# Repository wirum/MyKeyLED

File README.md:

# MyKeyLED
Your Pixels, Our Keychain  A simple OLED keychain that you can customize easily to your liking with GIFs, images, or short videos.

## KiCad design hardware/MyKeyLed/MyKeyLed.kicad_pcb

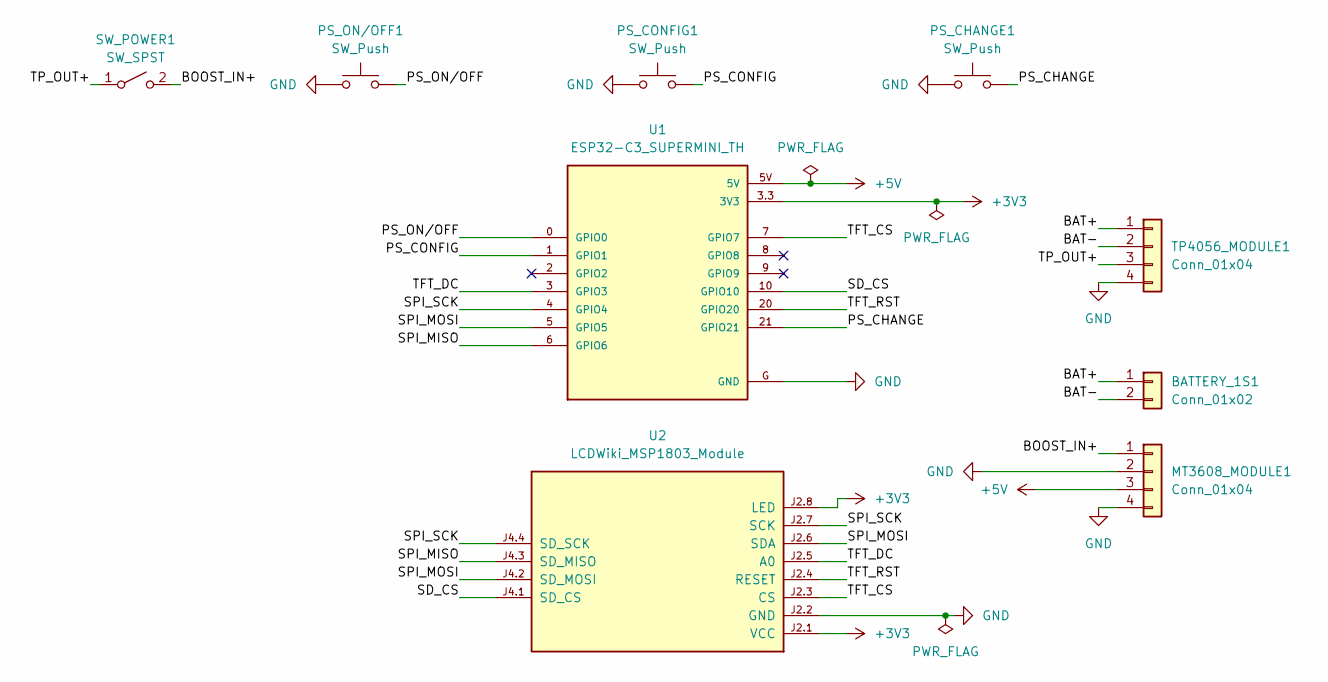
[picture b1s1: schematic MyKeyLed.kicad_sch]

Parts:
BATTERY_1S1: Conn_01x02; Battery_2Wire_2.54mm
MT3608_MODULE1: Conn_01x04; MT3608_Module_37x17mm
PS_CHANGE1: SW_Push; SW_PUSH-12mm
PS_CONFIG1: SW_Push; SW_PUSH-12mm
PS_ON/OFF1: SW_Push; SW_PUSH-12mm
SW_POWER1: SW_SPST; Switch_2Wire_2.54mm
TP4056_MODULE1: Conn_01x04; TP4056_USB-C_Protected_26x17mm
U1: ESP32-C3_SUPERMINI_TH; MODULE_ESP32-C3_SUPERMINI_TH
U2: LCDWiki_MSP1803_Module; LCDWiki_MSP1803_34.5x58mm

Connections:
+3V3: U1.3.3 (3V3), U2.J2.1 (VCC), U2.J2.8 (LED)
+5V: MT3608_MODULE1.3, U1.5V
/BAT+: BATTERY_1S1.1, TP4056_MODULE1.1
/BAT-: BATTERY_1S1.2, TP4056_MODULE1.2
/BOOST_IN+: MT3608_MODULE1.1, SW_POWER1.2 (B)
/PS_CHANGE: PS_CHANGE1.2, U1.21 (GPIO21)
/PS_CONFIG: PS_CONFIG1.2, U1.1 (GPIO1)
/PS_ON/OFF: PS_ON/OFF1.2, U1.0 (GPIO0)
/SD_CS: U1.10 (GPIO10), U2.J4.1 (SD_CS)
/SPI_MISO: U1.6 (GPIO6), U2.J4.3 (SD_MISO)
/SPI_MOSI: U1.5 (GPIO5), U2.J2.6 (SDA), U2.J4.2 (SD_MOSI)
/SPI_SCK: U1.4 (GPIO4), U2.J2.7 (SCK), U2.J4.4 (SD_SCK)
/TFT_CS: U1.7 (GPIO7), U2.J2.3 (CS)
/TFT_DC: U1.3 (GPIO3), U2.J2.5 (A0)
/TFT_RST: U1.20 (GPIO20), U2.J2.4 (RESET)
/TP_OUT+: SW_POWER1.1 (A), TP4056_MODULE1.3
GND: MT3608_MODULE1.2, MT3608_MODULE1.4, PS_CHANGE1.1, PS_CONFIG1.1, PS_ON/OFF1.1, TP4056_MODULE1.4, U1.G (GND), U2.J2.2 (GND)

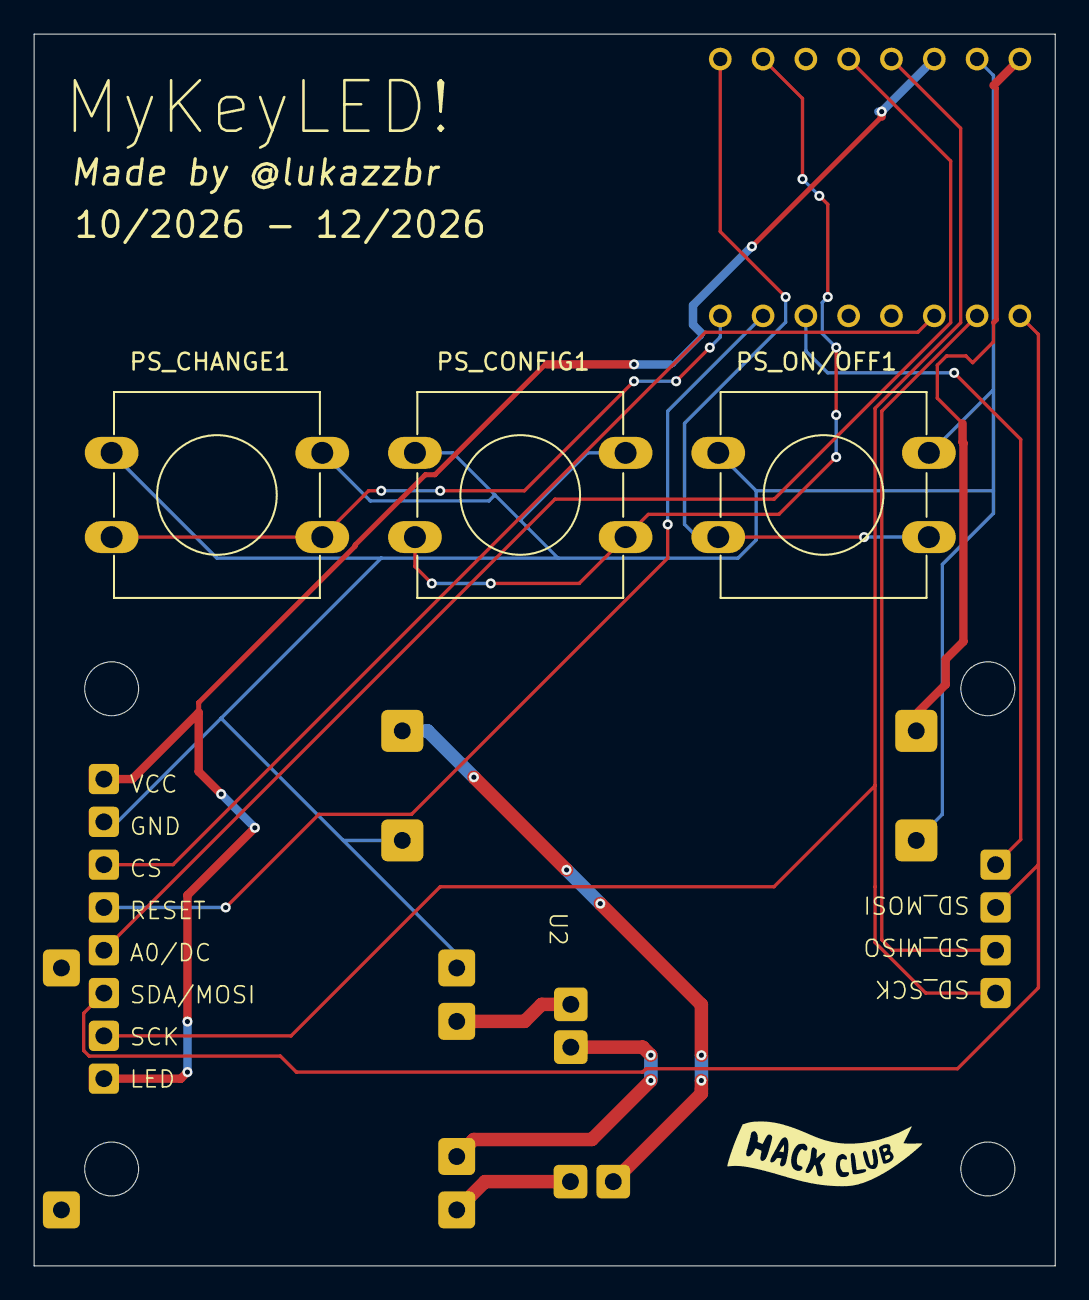
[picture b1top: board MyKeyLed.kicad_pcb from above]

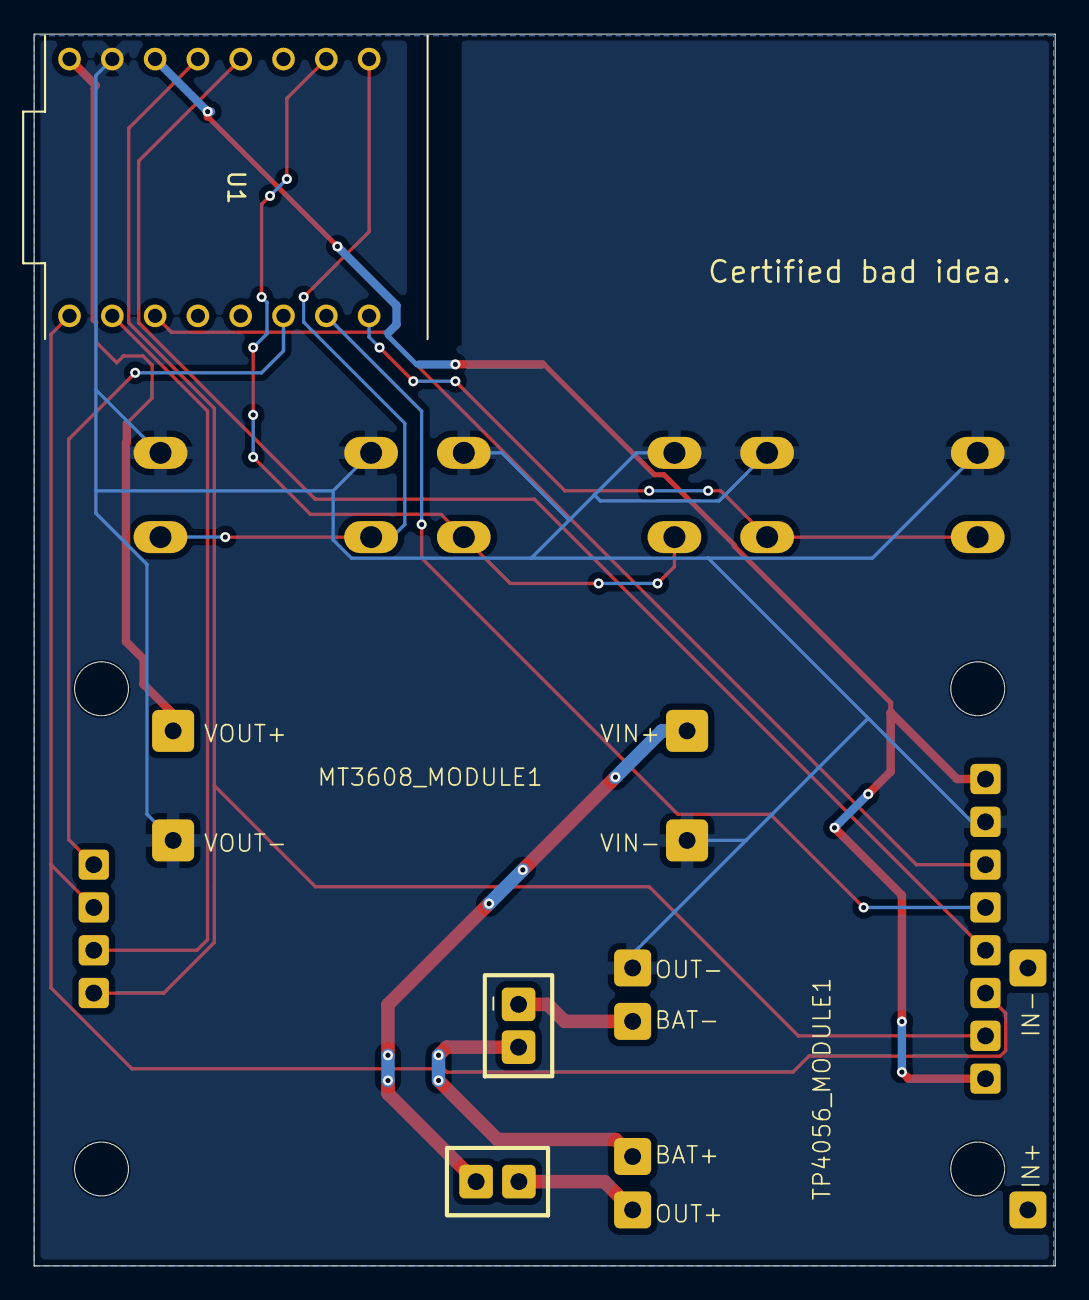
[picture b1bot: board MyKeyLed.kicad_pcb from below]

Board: 2 copper layers, 60.6 x 73.1 mm, 9 parts (5 on the bottom side), 17 nets.
